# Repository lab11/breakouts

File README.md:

breakouts
=========

A collection of very simple boards that often do slightly more than just breakout a chip

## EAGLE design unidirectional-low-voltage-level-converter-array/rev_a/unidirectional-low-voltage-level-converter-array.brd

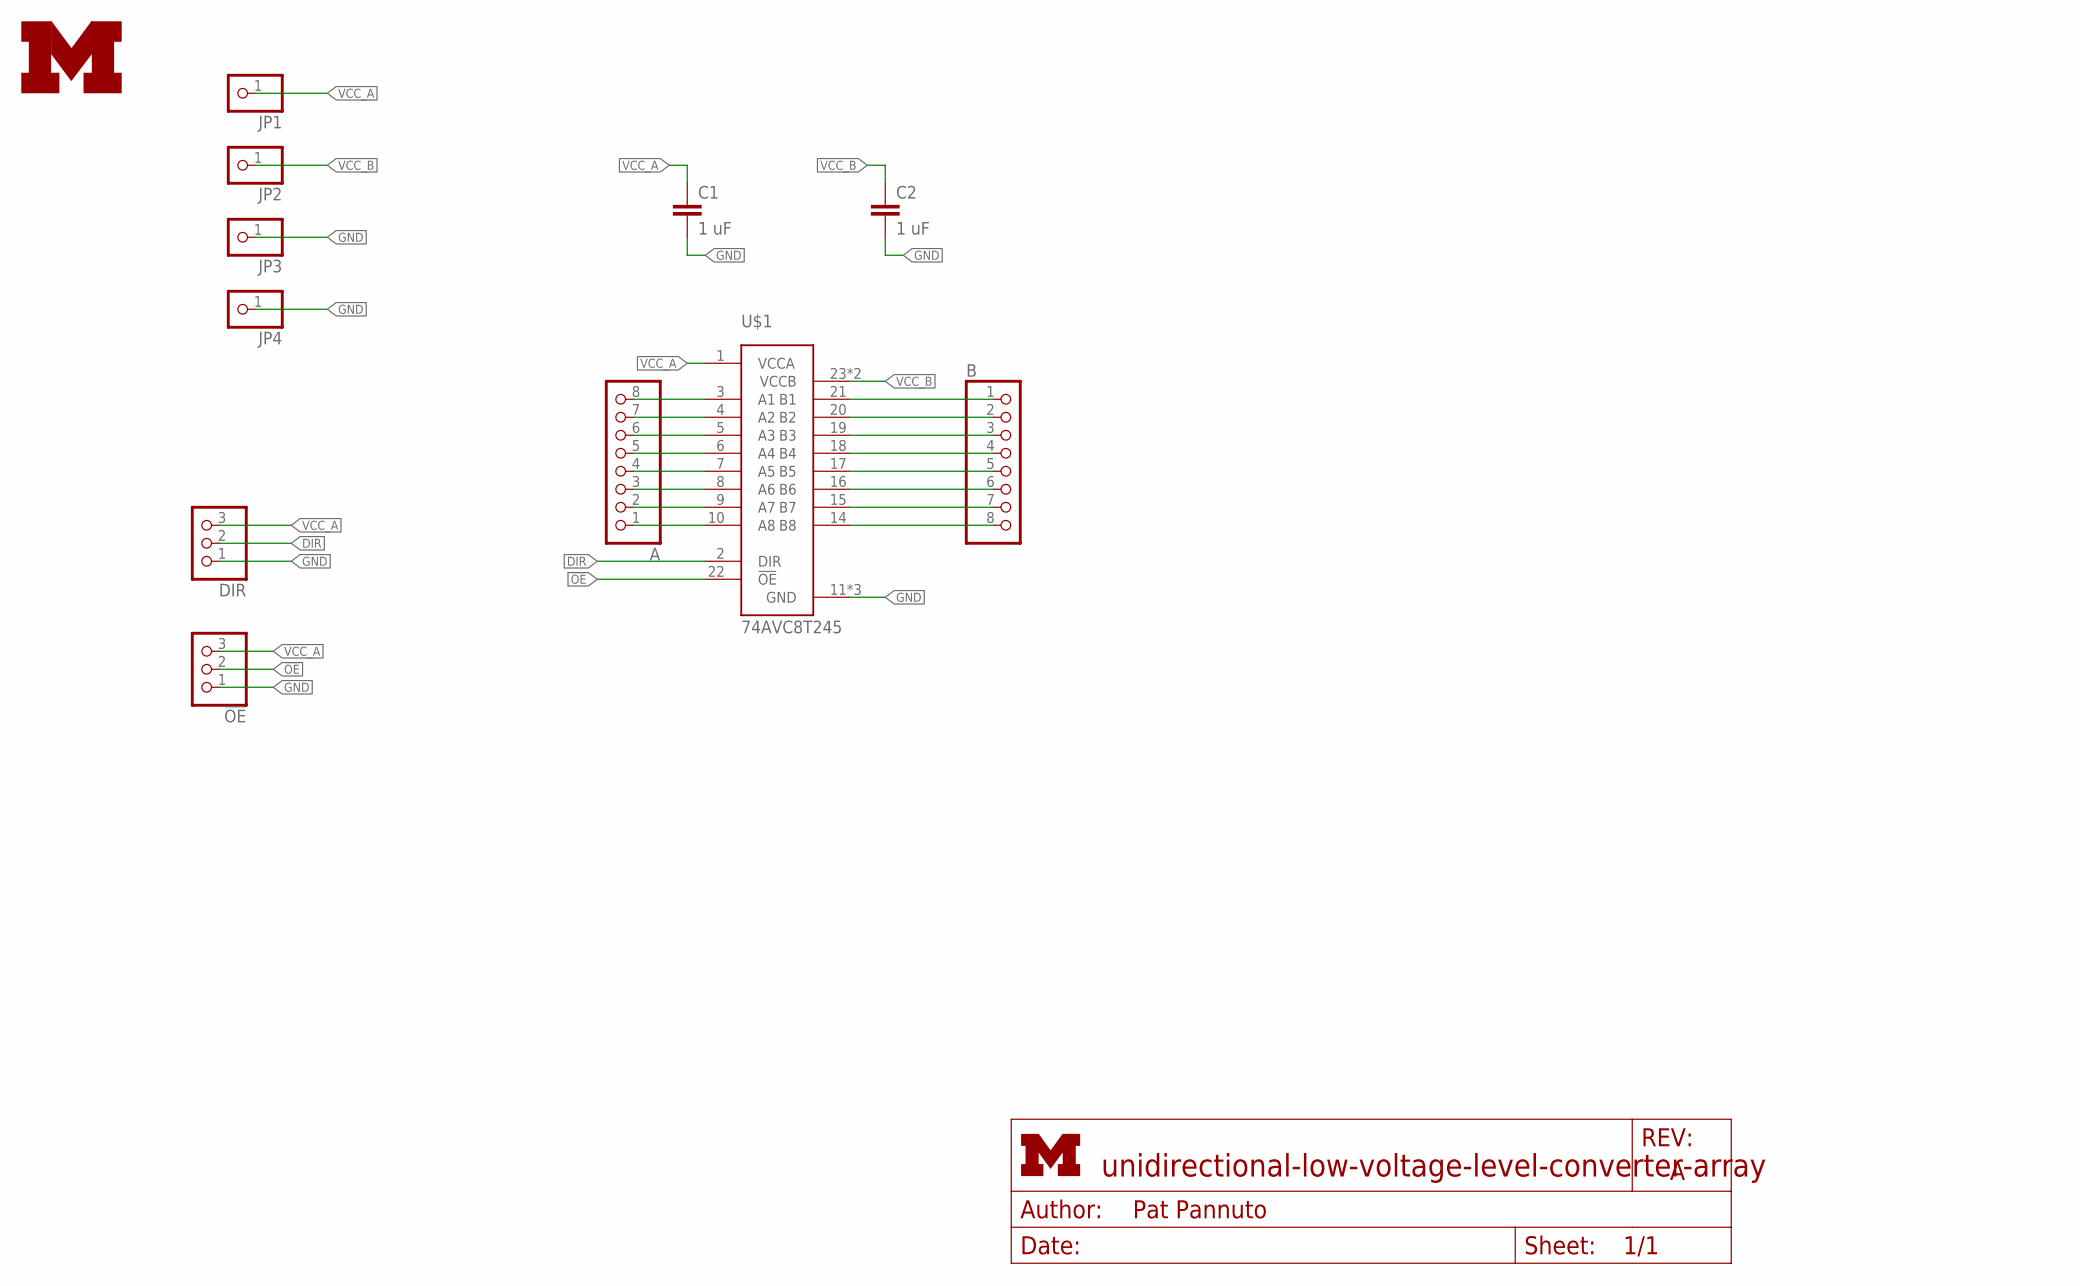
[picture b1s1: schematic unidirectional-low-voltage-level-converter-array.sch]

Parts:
!OE: PINHD-1X3; 1X03
A: PINHD-1X8; 1X08
B: PINHD-1X8; 1X08
C1, C2: 1 uF; C0603
DIR: PINHD-1X3; 1X03
JP1, JP2, JP3, JP4: PINHD-1X1; 1X01
LOGO1: UMICH_SOLID_SMALL+; UMICH_SOLID_100MIL
U$1: 74AVC8T245; TSSOP24

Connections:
!OE: !OE.2, U$1.22 (!OE)
A1: A.8, U$1.3 (A1)
A2: A.7, U$1.4 (A2)
A3: A.6, U$1.5 (A3)
A4: A.5, U$1.6 (A4)
A5: A.4, U$1.7 (A5)
A6: A.3, U$1.8 (A6)
A7: A.2, U$1.9 (A7)
A8: A.1, U$1.10 (A8)
B1: B.1, U$1.21 (B1)
B2: B.2, U$1.20 (B2)
B3: B.3, U$1.19 (B3)
B4: B.4, U$1.18 (B4)
B5: B.5, U$1.17 (B5)
B6: B.6, U$1.16 (B6)
B7: B.7, U$1.15 (B7)
B8: B.8, U$1.14 (B8)
DIR: DIR.2, U$1.2 (DIR)
GND: !OE.1, C1.2, C2.2, DIR.1, JP3.1, JP4.1, U$1.11 (GND), U$1.12 (GND), U$1.13 (GND)
VCC_A: !OE.3, C1.1, DIR.3, JP1.1, U$1.1 (VCCA)
VCC_B: C2.1, JP2.1, U$1.23 (VCCB), U$1.24 (VCCB)

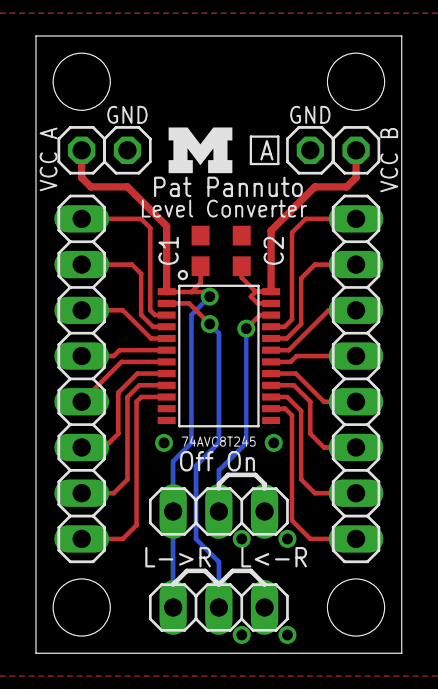
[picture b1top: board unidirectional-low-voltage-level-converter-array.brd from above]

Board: 2 copper layers, 20.3 x 34.3 mm, 12 parts (0 on the bottom side), 21 nets.

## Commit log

2014-02-05 Add level coverter breakout
2014-02-05 Ignore built output
2014-02-05 Add to fab copies
2014-02-05 Add missing silkscreen
    Labels for VCC and GND weren't included before. Now they are.
2014-02-05 Restrict stop layers to board dim, clean up silkscreen
    The stop layer isn't clipped by the CAM job, so do it by hand.
    Make Brad a little happier on the silkscreen. Whatever Brad, it was fine.
    Put the bottom left corner on the origin.
2014-02-05 JK, actually run the CAM jobs
